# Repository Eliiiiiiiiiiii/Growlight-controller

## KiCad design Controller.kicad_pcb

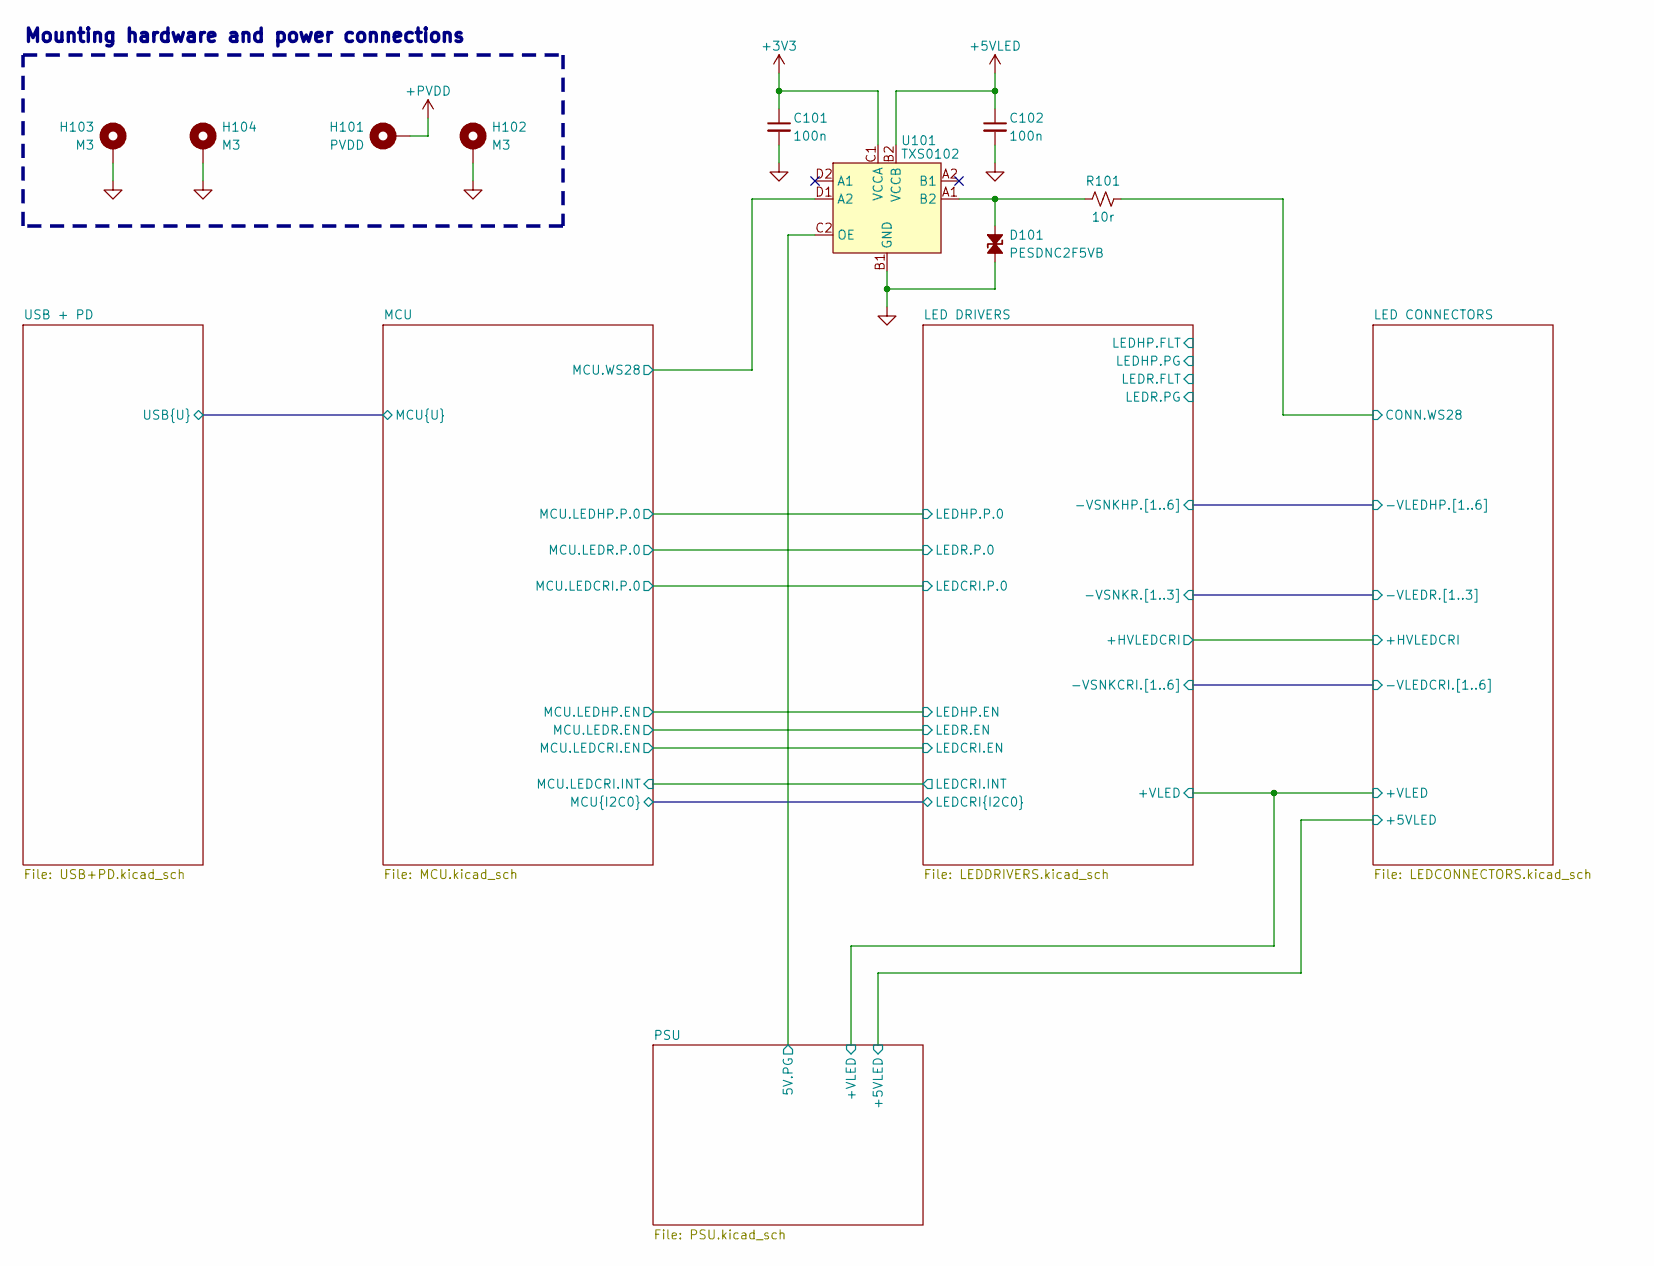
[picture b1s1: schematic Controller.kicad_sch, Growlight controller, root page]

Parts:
C101, C102: 100n; C 0402 (1005 Metric)
D101: PESDNC2F5VB; DFN-1006-2L
H101: PVDD; SMTSO3015CTJ
H102, H103, H104: M3; SMTSO3015CTJ
R101: 10r; R 0402 (1005 Metric)
U101: TXS0102; DSBGA-8 (0.9x1.9) P0.5

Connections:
+3V3: C101.1, U101.C1 (VCCA); also elsewhere on the board
+5VLED: C102.1, U101.B2 (VCCB); also elsewhere on the board
+PVDD: H101.1 (1_1); also elsewhere on the board
/LED CONNECTORS/CONN.WS28: R101.2; also elsewhere on the board
/MCU/MCU.WS28: U101.D1 (A2); also elsewhere on the board
/PSU/5V.PG: U101.C2 (OE); also elsewhere on the board
GND: C101.2, C102.2, D101.2 (A2), H102.1 (1_1), H103.1 (1_1), H104.1 (1_1), U101.B1 (GND); also elsewhere on the board
unnamed: D101.1 (A1), R101.1, U101.A1 (B2)

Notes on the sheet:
Mounting hardware and power connections

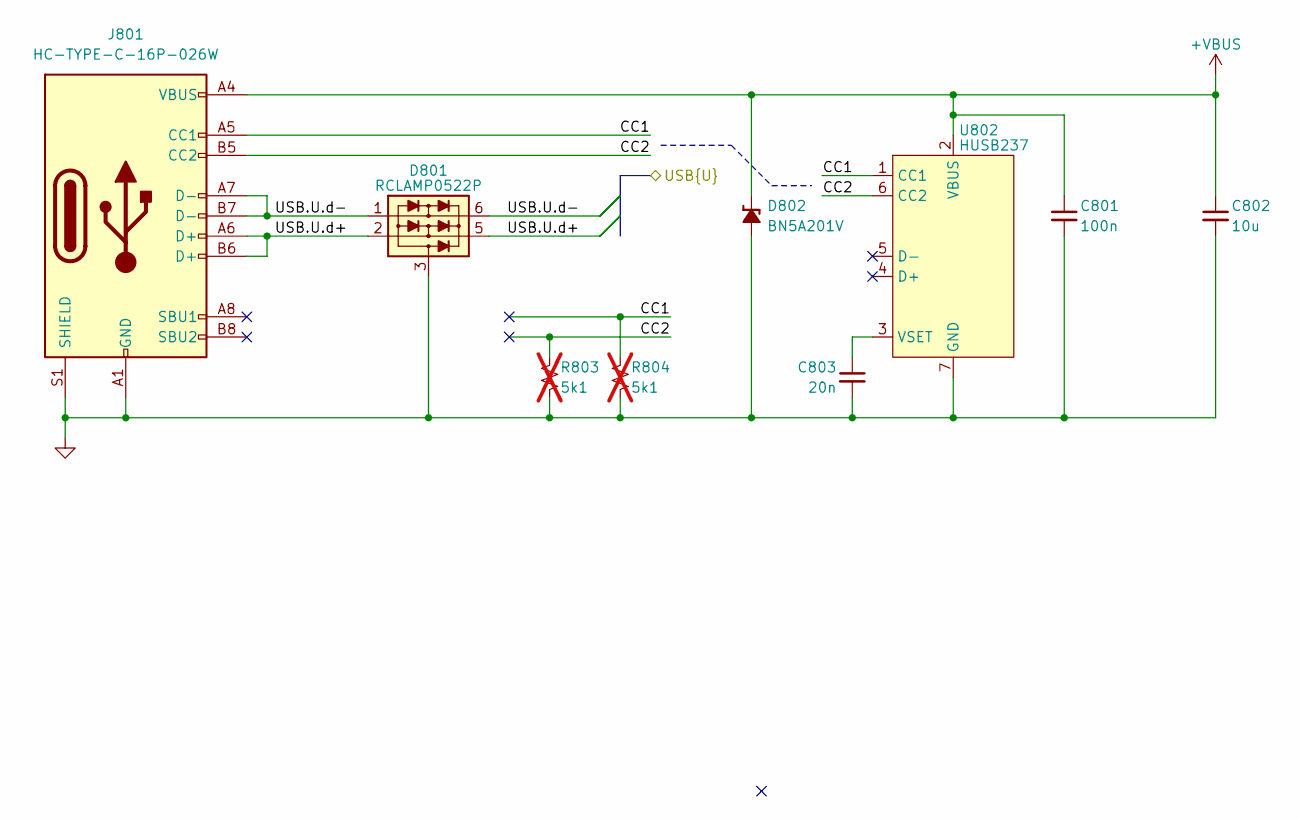
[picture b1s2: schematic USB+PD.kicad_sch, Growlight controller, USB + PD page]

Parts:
C801: 100n; C 0402 (1005 Metric)
C802: 10u; C 0805 (2012 Metric)
C803: 20n; C 0402 (1005 Metric)
D801: RCLAMP0522P; DFN1610-6L (1.6x1)
D802: BN5A201V; DFN1610-2L (1.6x1)
J801: HC-TYPE-C-16P-026W
R803, R804: 5k1; R 0402 (1005 Metric); not fitted
U802: HUSB237; SON-6 (2x2) P0.65

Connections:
+VBUS: C801.1, C802.1, D802.1 (K), J801.A4 (VBUS), J801.A9 (VBUS), J801.B4 (VBUS), J801.B9 (VBUS), U802.2 (VBUS); also elsewhere on the board
/MCU/MCU.U.d+: D801.2, D801.5, J801.A6 (D+), J801.B6 (D+); also elsewhere on the board
/MCU/MCU.U.d-: D801.1, D801.6, J801.A7 (D-), J801.B7 (D-); also elsewhere on the board
/USB + PD/CC1: J801.A5 (CC1), R804.1, U802.1 (CC1)
/USB + PD/CC2: J801.B5 (CC2), R803.1, U802.6 (CC2)
GND: C801.2, C802.2, C803.2, D801.3, D801.4, D802.2 (A), J801.A1 (GND), J801.A12 (GND), J801.B1 (GND), J801.B12 (GND), J801.S1 (SHIELD), R803.2, R804.2, U802.7 (GND); also elsewhere on the board
unnamed: C803.1, U802.3 (VSET)

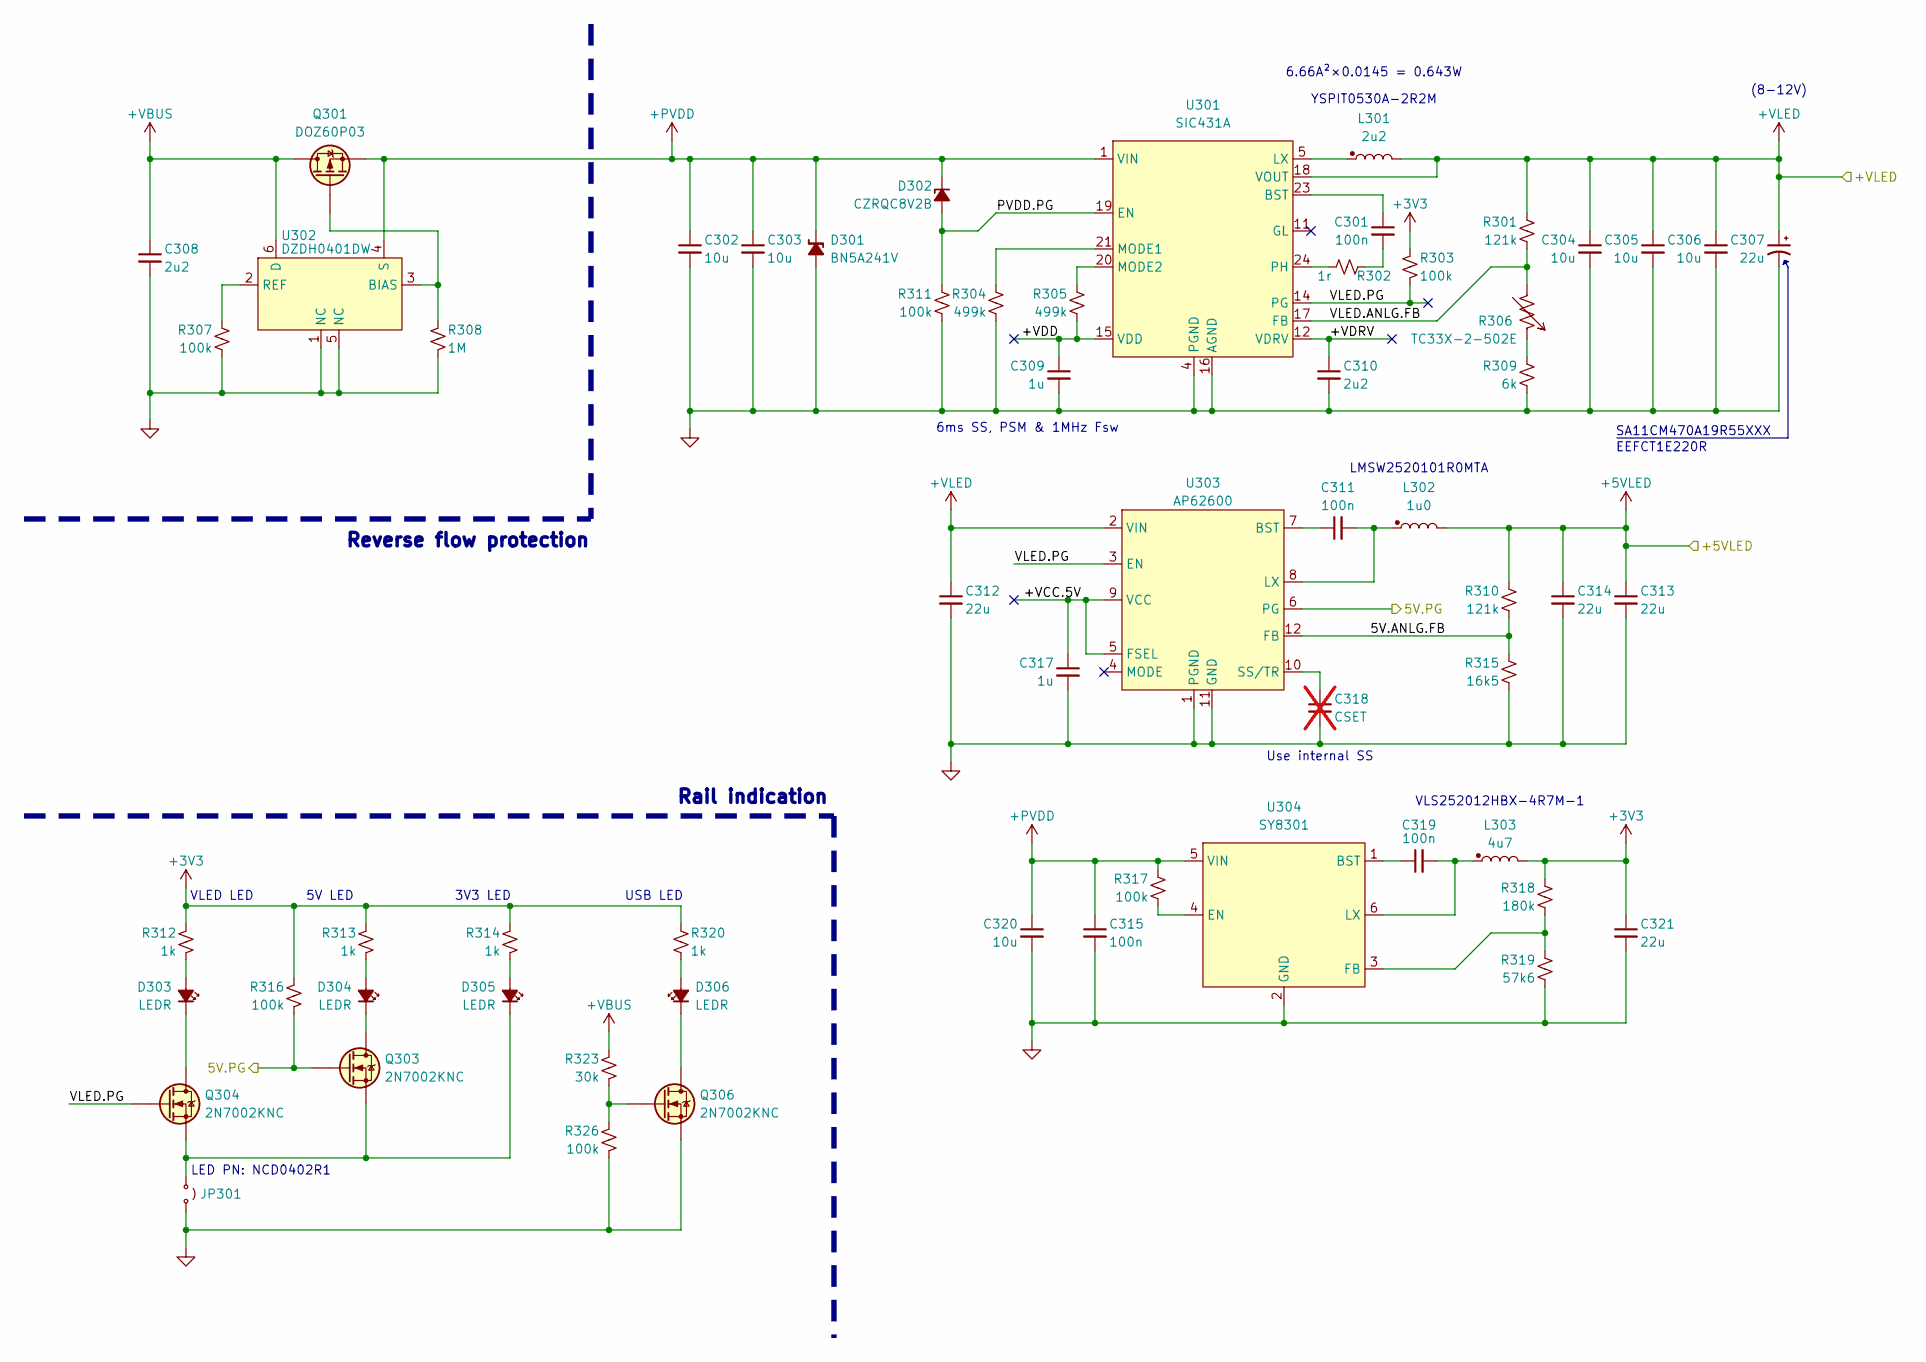
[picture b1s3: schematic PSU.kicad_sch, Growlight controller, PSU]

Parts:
C301, C311, C315, C319: 100n; C 0402 (1005 Metric)
C302, C303, C304, C305, C306, C320: 10u; C 0805 (2012 Metric)
C307: 22u; CP Flat (7.3x4.3) H1.4 muRata
C308, C310: 2u2; C 0603 (1608 Metric)
C309, C317: 1u; C 0402 (1005 Metric)
C312, C313, C314, C321: 22u; C 0805 (2012 Metric)
C318: CSET; C 0402 (1005 Metric); not fitted
D301: BN5A241V; DFN1610-2L (1.6x1)
D302: CZRQC8V2B; DFN-1006-2L
D303, D304, D305, D306: LEDR; LED-0402-R
JP301: Jumper_2_Small_Open; Jumper-NO 2P (1.9x1.4)
L301: 2u2; YSPIT0530A
L302: 1u0; LMSW252010
L303: 4u7; VLS252012
Q301: DOZ60P03; DFN-8 (3x3) 1EP
Q303, Q304, Q306: 2N7002KNC; DFN-1006-3L
R301, R310: 121k; R 0402 (1005 Metric)
R302: 1r; R 0402 (1005 Metric)
R303, R307, R311, R316, R317, R326: 100k; R 0402 (1005 Metric)
R304, R305: 499k; R 0402 (1005 Metric)
R306: TC33X-2-502E; TC33X-x-xxxx
R308: 1M; R 0402 (1005 Metric)
R309: 6k; R 0402 (1005 Metric)
R312, R313, R314, R320: 1k; R 0402 (1005 Metric)
R315: 16k5; R 0402 (1005 Metric)
R318: 180k; R 0402 (1005 Metric)
R319: 57k6; R 0402 (1005 Metric)
R323: 30k; R 0402 (1005 Metric)
U301: SIC431A; MLP44-24L (4x4) P0.45 Vishay
U302: DZDH0401DW; SOT-363
U303: AP62600; VQFN2030-12 (2x3) P0.5 DIODES
U304: SY8301; SOT-23-6

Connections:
+3V3: C321.1, L303.2, R303.1, R312.2, R313.2, R314.2, R316.2, R318.1, R320.2; also elsewhere on the board
+5VLED: C313.1, C314.1, L302.2, R310.1; also elsewhere on the board
+PVDD: C302.1, C303.1, C315.1, C320.1, D301.1 (K), D302.1 (K), Q301.1 (S), Q301.2 (S), Q301.3 (S), R317.1, U301.1 (VIN), U301.2 (VIN), U301.22 (VIN), U301.26 (VIN), U302.4 (S), U304.5 (VIN); also elsewhere on the board
+VBUS: C308.1, Q301.5 (D), R323.2, U302.6 (D); also elsewhere on the board
+VLED: C304.1, C305.1, C306.1, C307.1, C312.1, L301.2, R301.1, U301.18 (VOUT), U303.2 (VIN); also elsewhere on the board
/PSU/5V.ANLG.FB: R310.2, R315.1, U303.12 (FB)
/PSU/5V.PG: Q303.1 (G), R316.1, U303.6 (PG); also elsewhere on the board
/PSU/+VCC.5V: C317.1, U303.5 (FSEL), U303.9 (VCC)
/PSU/+VDD: C309.1, R305.2, U301.15 (VDD)
/PSU/+VDRV: C310.1, U301.12 (VDRV)
/PSU/PVDD.PG: D302.2 (A), R311.1, U301.19 (EN)
/PSU/VLED.ANLG.FB: R301.2, R306.2, U301.17 (FB)
/PSU/VLED.PG: Q304.1 (G), R303.2, U301.14 (PG), U303.3 (EN)
GND: C302.2, C303.2, C304.2, C305.2, C306.2, C307.2, C308.2, C309.2, C310.2, C312.2, C313.2, C314.2, C315.2, C317.2, C318.2, C320.2, C321.2, D301.2 (A), JP301.1 (A), Q306.2 (S), R304.2, R307.2, R308.2, R309.2, R311.2, R315.2, R319.2, R326.1, U301.3 (PGND), U301.4 (PGND), U301.13 (PGND), U301.16 (AGND), U301.25 (AGND), U301.27 (PGND), U302.1 (NC), U302.5 (NC), U303.1 (PGND), U303.11 (GND), U304.2 (GND); also elsewhere on the board
unnamed: C301.2, R302.2
unnamed: D303.2 (A), R312.1
unnamed: D303.1 (K), Q304.3 (D)
unnamed: D304.2 (A), R313.1
unnamed: D304.1 (K), Q303.3 (D)
unnamed: D305.2 (A), R314.1
unnamed: D305.1 (K), JP301.2 (B), Q303.2 (S), Q304.2 (S)
unnamed: D306.2 (A), R320.1
unnamed: D306.1 (K), Q306.3 (D)
unnamed: L301.1, U301.5 (LX), U301.6 (LX), U301.7 (LX), U301.8 (LX), U301.9 (LX)
unnamed: Q301.4 (G), R308.1, U302.3 (BIAS)
unnamed: Q306.1 (G), R323.1, R326.2
unnamed: R306.1, R309.1
unnamed: C301.1, U301.23 (BST)
unnamed: R304.1, U301.21 (MODE1)
unnamed: R305.1, U301.20 (MODE2)
unnamed: R302.1, U301.24 (PH)
unnamed: R307.1, U302.2 (REF)
unnamed: C311.1, U303.7 (BST)
unnamed: C311.2, L302.1, U303.8 (LX)
unnamed: C318.1, U303.10 (SS/TR)
unnamed: C319.1, U304.1 (BST)
unnamed: R317.2, U304.4 (EN)
unnamed: R318.2, R319.1, U304.3 (FB)
unnamed: C319.2, L303.1, U304.6 (LX)

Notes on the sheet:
5V LED
Reverse flow protection
VLS252012HBX-4R7M-1
LED PN: NCD0402R1
USB LED
3V3 LED
EEFCT1E220R
(8-12V)
Rail indication
YSPIT0530A-2R2M
SA11CM470A19R55XXX
VLED LED
LMSW2520101R0MTA
6.66A²×0.0145 = 0.643W
6ms SS, PSM & 1MHz Fsw
Use internal SS

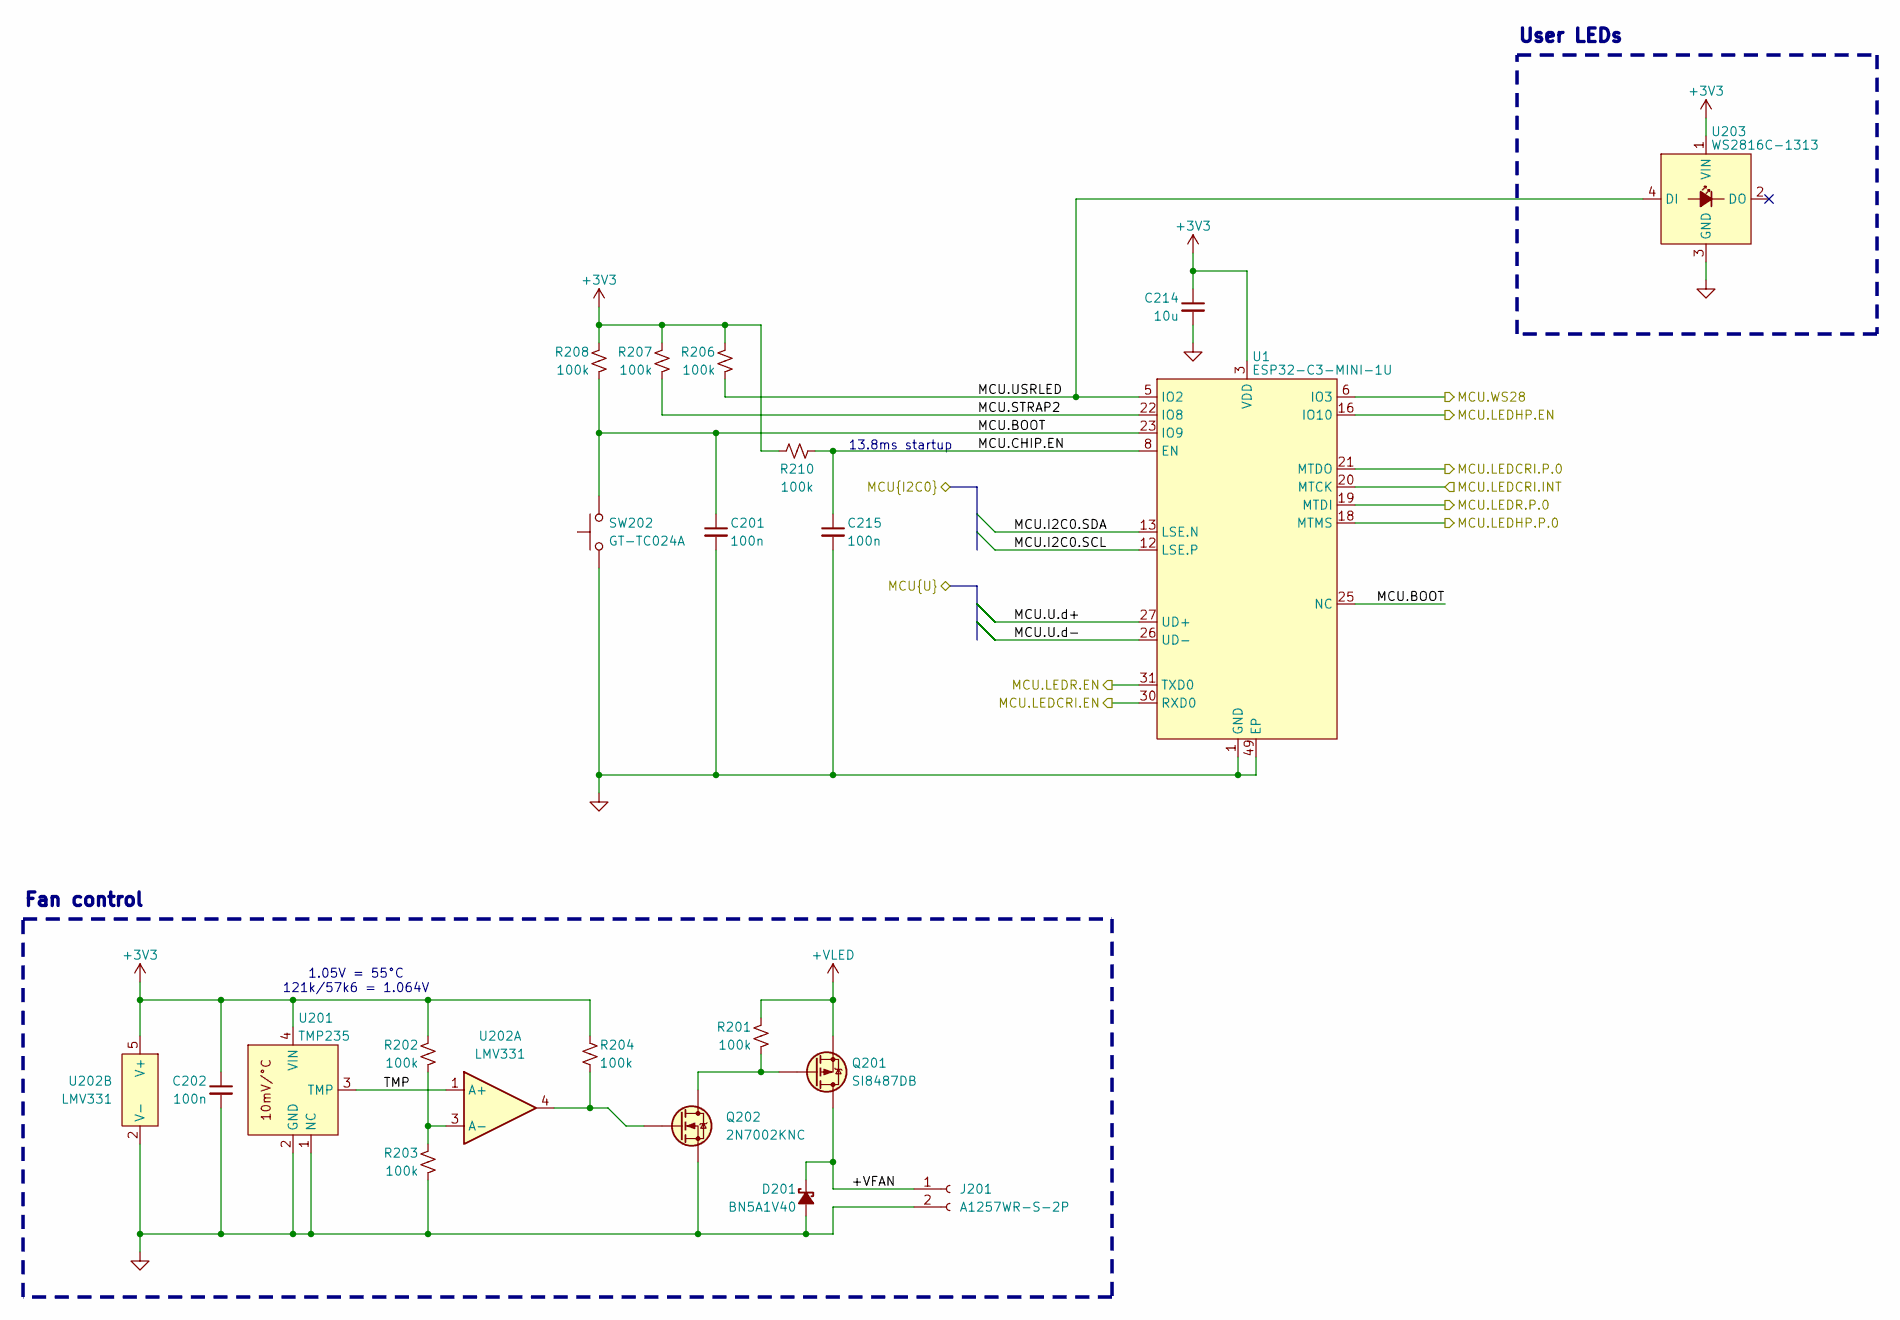
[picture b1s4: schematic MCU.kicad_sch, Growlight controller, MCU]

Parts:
C201, C202, C215: 100n; C 0402 (1005 Metric)
C214: 10u; C 0805 (2012 Metric)
D201: BN5A1V40; DFN1610-2L (1.6x1)
J201: A1257WR-S-2P; A1257WR-S-2P (GH)
Q201: SI8487DB; WLCSP-4 (1.56x1.56) P0.8
Q202: 2N7002KNC; DFN-1006-3L
R201, R202, R203, R204, R206, R207, R208, R210: 100k; R 0402 (1005 Metric)
SW202: GT-TC024A; GT-TC024A-H0060-L1
U1: ESP32-C3-MINI-1U
U201: TMP235; SOT-363-5
U202: LMV331; SOT-363-5
U203: WS2816C-1313; WS2816C-1313 4P

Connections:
+3V3: C202.1, C214.1, R202.2, R204.2, R206.2, R207.2, R208.2, R210.1, U1.3 (VDD), U201.4 (VIN), U202.5 (V+), U203.1 (VIN); also elsewhere on the board
+VLED: Q201.4 (S), R201.2; also elsewhere on the board
/LED DRIVERS/LEDCRI.EN: U1.30 (RXD0); also elsewhere on the board
/LED DRIVERS/LEDCRI.I2C0.SCL: U1.12 (LSE.P); also elsewhere on the board
/LED DRIVERS/LEDCRI.I2C0.SDA: U1.13 (LSE.N); also elsewhere on the board
/LED DRIVERS/LEDCRI.INT: U1.20 (MTCK); also elsewhere on the board
/LED DRIVERS/LEDCRI.P.0: U1.21 (MTDO); also elsewhere on the board
/LED DRIVERS/LEDHP.EN: U1.16 (IO10); also elsewhere on the board
/LED DRIVERS/LEDHP.P.0: U1.18 (MTMS); also elsewhere on the board
/LED DRIVERS/LEDR.EN: U1.31 (TXD0); also elsewhere on the board
/LED DRIVERS/LEDR.P.0: U1.19 (MTDI); also elsewhere on the board
/MCU/+VFAN: D201.1 (K), J201.1, Q201.2 (D), Q201.3 (D)
/MCU/MCU.BOOT: C201.1, R208.1, SW202.2, U1.23 (IO9), U1.25 (NC)
/MCU/MCU.CHIP.EN: C215.1, R210.2, U1.8 (EN)
/MCU/MCU.STRAP2: R207.1, U1.22 (IO8)
/MCU/MCU.U.d+: U1.27 (UD+); also elsewhere on the board
/MCU/MCU.U.d-: U1.26 (UD-); also elsewhere on the board
/MCU/MCU.USRLED: R206.1, U1.5 (IO2), U203.4 (DI)
/MCU/MCU.WS28: U1.6 (IO3); also elsewhere on the board
/MCU/TMP: U201.3 (TMP), U202.1 (A+)
GND: C201.2, C202.2, C214.2, C215.2, D201.2 (A), J201.2, Q202.2 (S), R203.1, SW202.1, U1.1 (GND), U1.2 (GND), U1.11 (GND), U1.14 (GND), U1.36 (GND), U1.37 (GND), U1.38 (GND), U1.39 (GND), U1.40 (GND), U1.41 (GND), U1.42 (GND), U1.43 (GND), U1.44 (GND), U1.45 (GND), U1.46 (GND), U1.47 (GND), U1.48 (GND), U1.49 (EP), U1.50 (GND), U1.51 (GND), U1.52 (GND), U1.53 (GND), U201.1 (NC), U201.2 (GND), U201.5 (NC), U202.2 (V-), U203.3 (GND); also elsewhere on the board
unnamed: Q201.1 (G), Q202.3 (D), R201.1
unnamed: Q202.1 (G), R204.1, U202.4
unnamed: R202.1, R203.2, U202.3 (A-)

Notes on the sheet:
1.05V = 55°C 121k/57k6 = 1.064V
User LEDs
13.8ms startup
Fan control

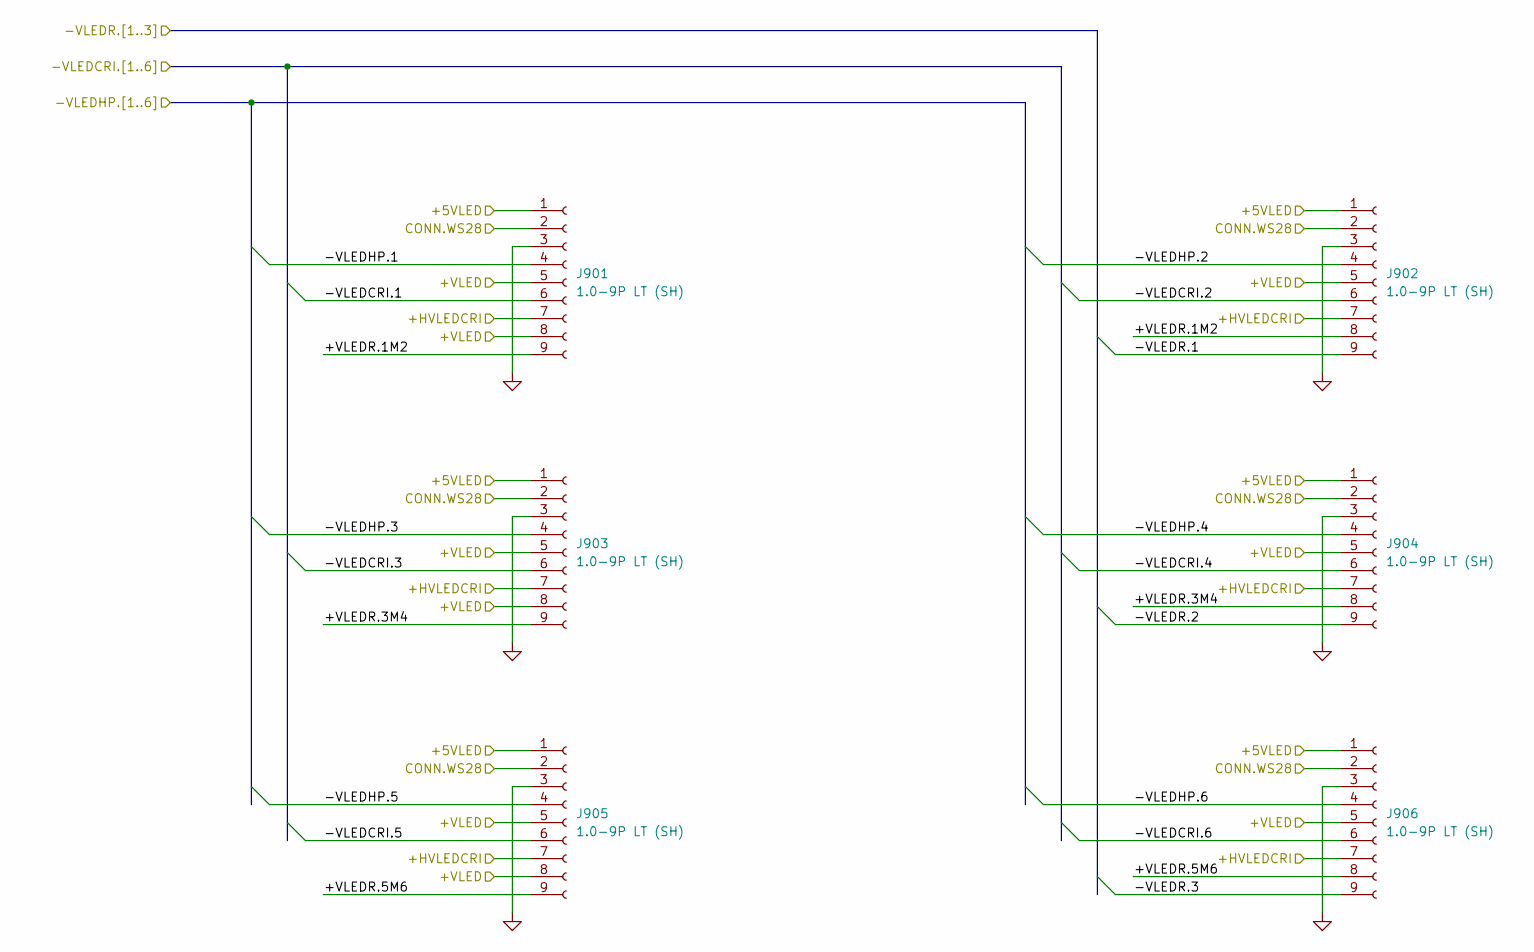
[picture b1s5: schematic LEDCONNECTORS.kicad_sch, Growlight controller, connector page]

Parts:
J901, J902, J903, J904, J905, J906: 1.0-9P LT (SH)

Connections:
+5VLED: J901.1, J902.1, J903.1, J904.1, J905.1, J906.1; also elsewhere on the board
+HVLEDCRI: J901.7, J902.7, J903.7, J904.7, J905.7, J906.7; also elsewhere on the board
+VLED: J901.5, J901.8, J902.5, J903.5, J903.8, J904.5, J905.5, J905.8, J906.5; also elsewhere on the board
/LED CONNECTORS/+VLEDR.1M2: J901.9, J902.8
/LED CONNECTORS/+VLEDR.3M4: J903.9, J904.8
/LED CONNECTORS/+VLEDR.5M6: J905.9, J906.8
/LED CONNECTORS/-VLEDCRI.1: J901.6; also elsewhere on the board
/LED CONNECTORS/-VLEDCRI.2: J902.6; also elsewhere on the board
/LED CONNECTORS/-VLEDCRI.3: J903.6; also elsewhere on the board
/LED CONNECTORS/-VLEDCRI.4: J904.6; also elsewhere on the board
/LED CONNECTORS/-VLEDCRI.5: J905.6; also elsewhere on the board
/LED CONNECTORS/-VLEDCRI.6: J906.6; also elsewhere on the board
/LED CONNECTORS/-VLEDHP.1: J901.4; also elsewhere on the board
/LED CONNECTORS/-VLEDHP.2: J902.4; also elsewhere on the board
/LED CONNECTORS/-VLEDHP.3: J903.4; also elsewhere on the board
/LED CONNECTORS/-VLEDHP.4: J904.4; also elsewhere on the board
/LED CONNECTORS/-VLEDHP.5: J905.4; also elsewhere on the board
/LED CONNECTORS/-VLEDHP.6: J906.4; also elsewhere on the board
/LED CONNECTORS/-VLEDR.1: J902.9; also elsewhere on the board
/LED CONNECTORS/-VLEDR.2: J904.9; also elsewhere on the board
/LED CONNECTORS/-VLEDR.3: J906.9; also elsewhere on the board
/LED CONNECTORS/CONN.WS28: J901.2, J902.2, J903.2, J904.2, J905.2, J906.2; also elsewhere on the board
GND: J901.3, J902.3, J903.3, J904.3, J905.3, J906.3; also elsewhere on the board

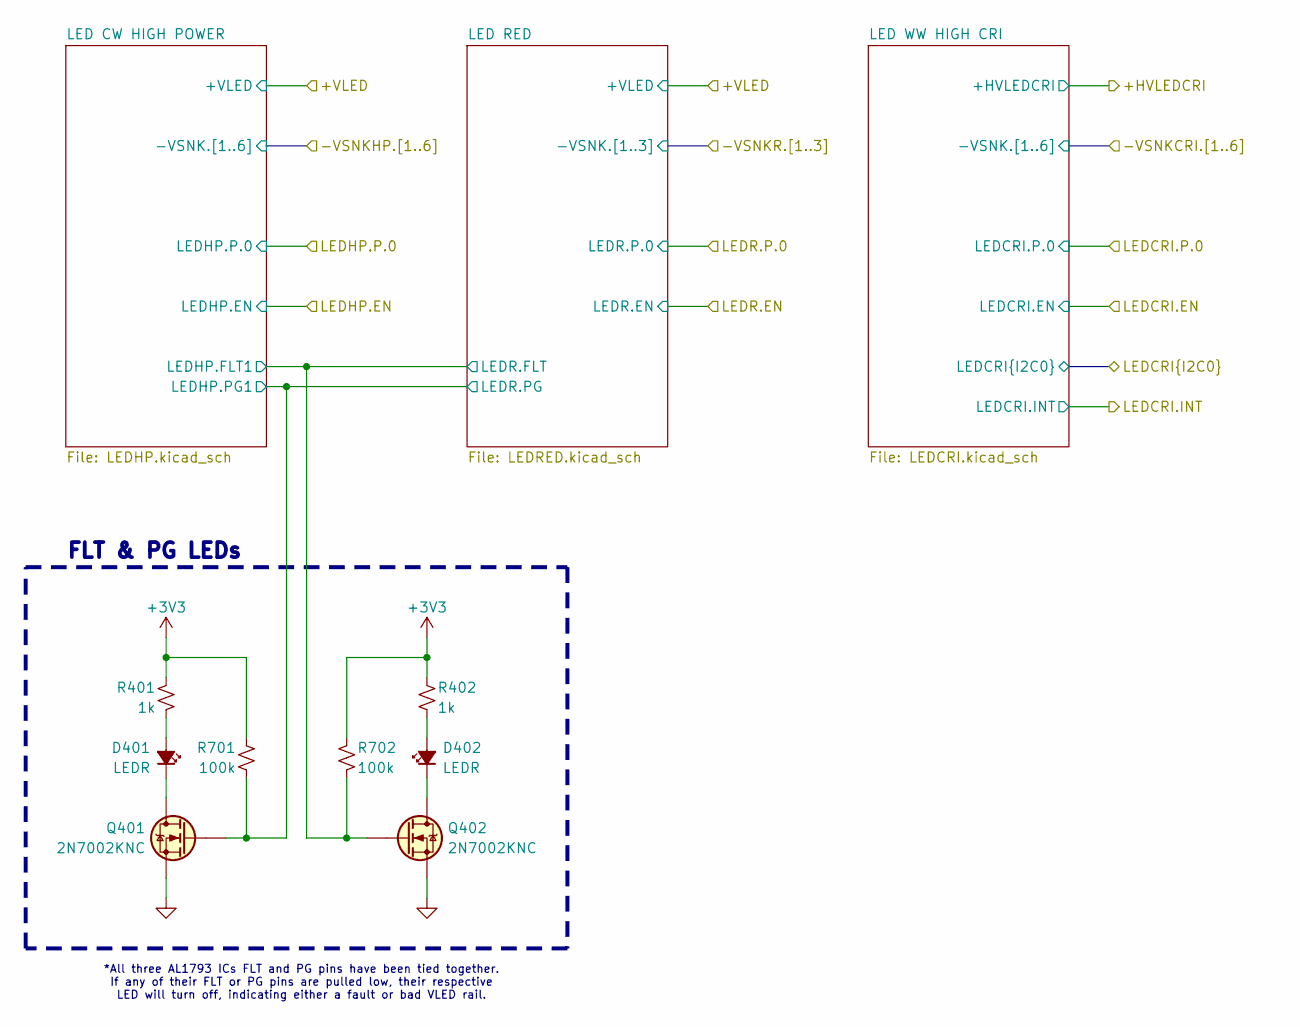
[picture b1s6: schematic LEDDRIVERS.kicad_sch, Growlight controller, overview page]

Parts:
D401, D402: LEDR; LED-0402-R
Q401, Q402: 2N7002KNC; DFN-1006-3L
R401, R402: 1k; R 0402 (1005 Metric)
R701, R702: 100k; R 0402 (1005 Metric)

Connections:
+3V3: R401.2, R402.2, R701.1, R702.1; also elsewhere on the board
/LED DRIVERS/LED CW HIGH POWER/LEDHP.FLT1: Q402.1 (G), R702.2; also elsewhere on the board
/LED DRIVERS/LED CW HIGH POWER/LEDHP.PG1: Q401.1 (G), R701.2; also elsewhere on the board
GND: Q401.2 (S), Q402.2 (S); also elsewhere on the board
unnamed: D401.2 (A), R401.1
unnamed: D401.1 (K), Q401.3 (D)
unnamed: D402.2 (A), R402.1
unnamed: D402.1 (K), Q402.3 (D)

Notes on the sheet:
*All three AL1793 ICs FLT and PG pins have been tied together. If any of their FLT or PG pins are pulled low, their respective LED will turn off, indicating either a fault or bad VLED rail.
FLT & PG LEDs

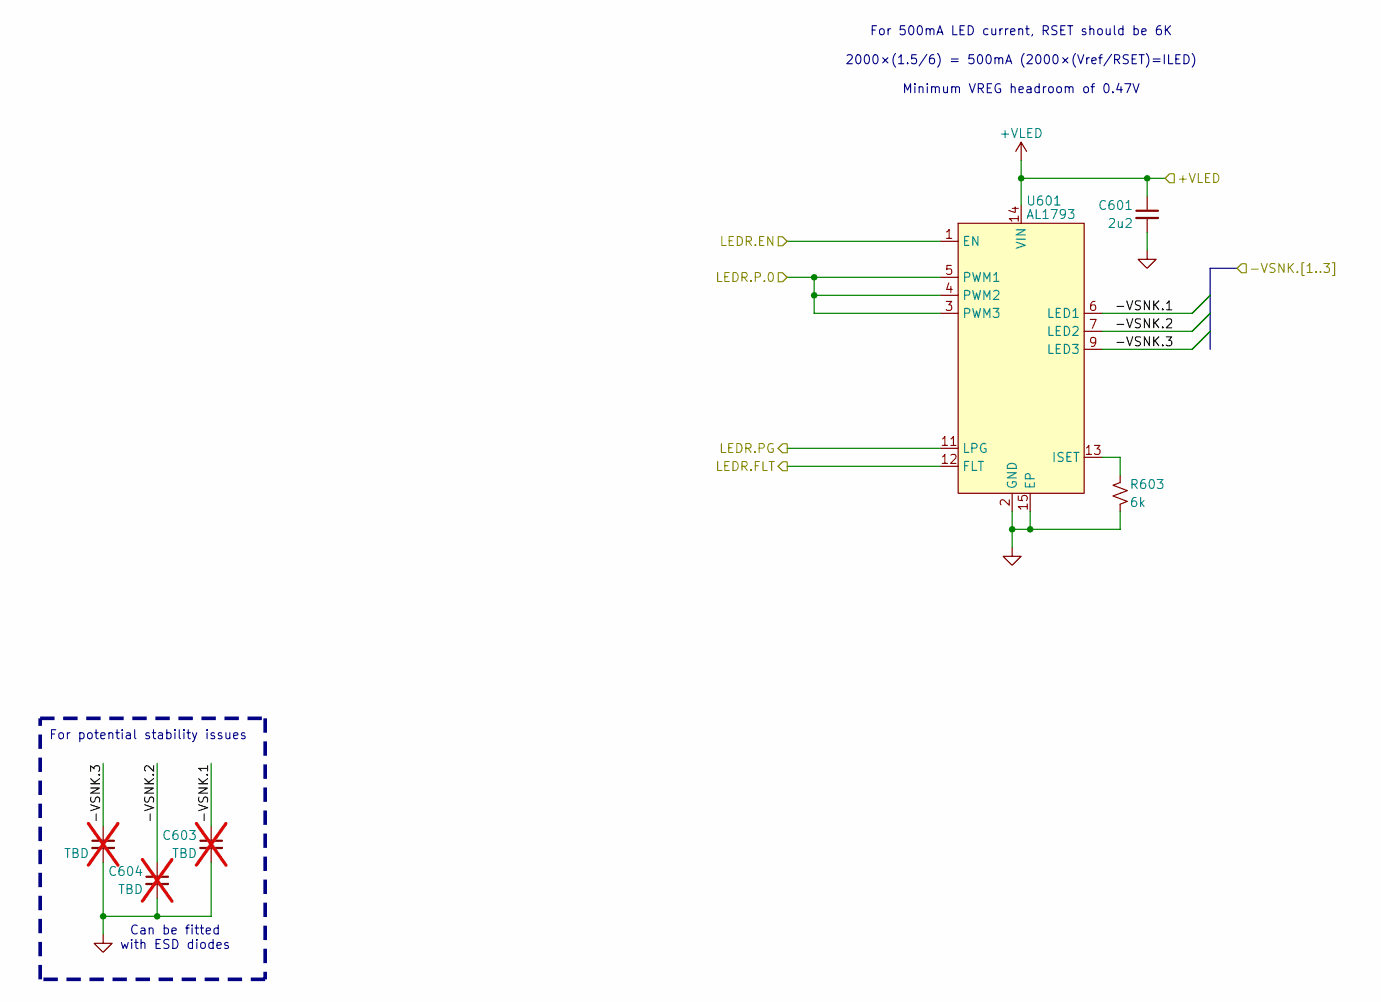
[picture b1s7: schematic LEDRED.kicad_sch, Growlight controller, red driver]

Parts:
C601: 2u2; C 0603 (1608 Metric)
C602, C603, C604: TBD; C 0402 (1005 Metric); not fitted
R603: 6k; R 0402 (1005 Metric)
U601: AL1793; UDFN4030-14 (3x4) 1EP

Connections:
+VLED: C601.1, U601.14 (VIN); also elsewhere on the board
/LED CONNECTORS/-VLEDR.1: C603.1, U601.6 (LED1); also elsewhere on the board
/LED CONNECTORS/-VLEDR.2: C604.1, U601.7 (LED2); also elsewhere on the board
/LED CONNECTORS/-VLEDR.3: C602.1, U601.9 (LED3); also elsewhere on the board
/LED DRIVERS/LED CW HIGH POWER/LEDHP.FLT1: U601.12 (FLT); also elsewhere on the board
/LED DRIVERS/LED CW HIGH POWER/LEDHP.PG1: U601.11 (LPG); also elsewhere on the board
/LED DRIVERS/LEDR.EN: U601.1 (EN); also elsewhere on the board
/LED DRIVERS/LEDR.P.0: U601.3 (PWM3), U601.4 (PWM2), U601.5 (PWM1); also elsewhere on the board
GND: C601.2, C602.2, C603.2, C604.2, R603.2, U601.2 (GND), U601.8 (GND), U601.10 (GND), U601.15 (EP); also elsewhere on the board
unnamed: R603.1, U601.13 (ISET)

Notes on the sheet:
For potential stability issues
Can be fitted with ESD diodes
For 500mA LED current, RSET should be 6K 2000×(1.5/6) = 500mA (2000×(Vref/RSET)=ILED) Minimum VREG headroom of 0.47V

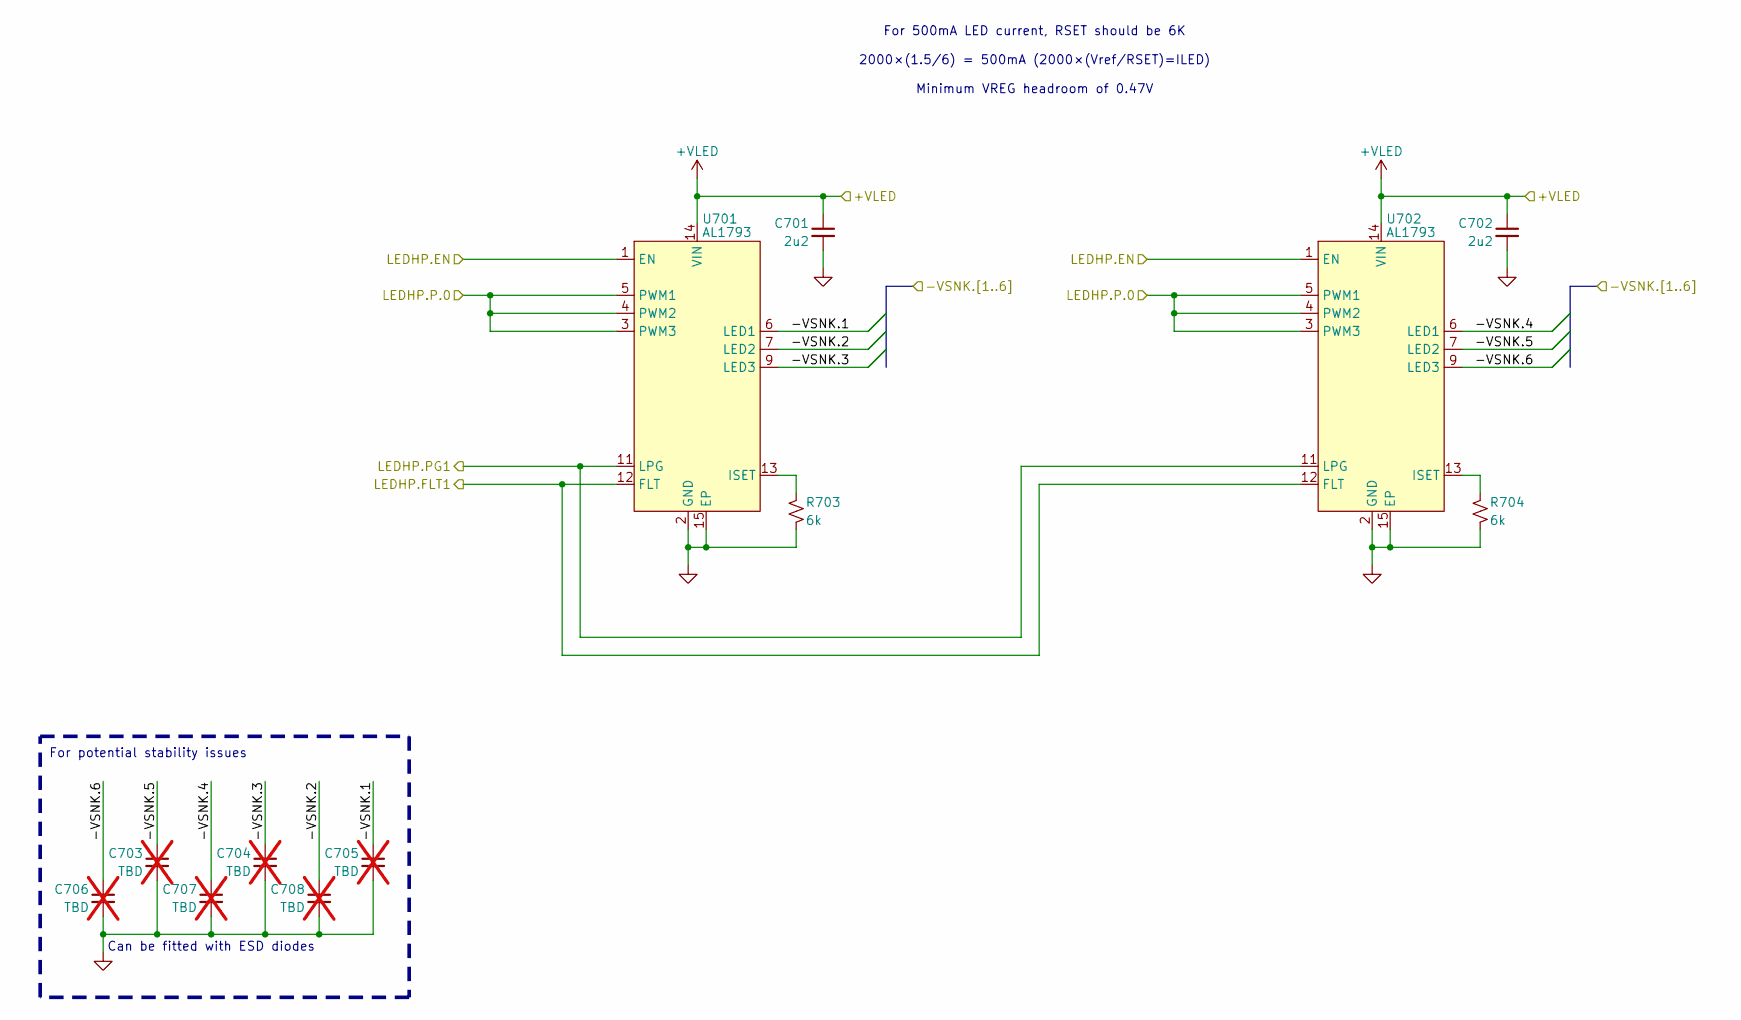
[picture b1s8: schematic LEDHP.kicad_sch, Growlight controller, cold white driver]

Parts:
C701, C702: 2u2; C 0603 (1608 Metric)
C703, C704, C705, C706, C707, C708: TBD; C 0402 (1005 Metric); not fitted
R703, R704: 6k; R 0402 (1005 Metric)
U701, U702: AL1793; UDFN4030-14 (3x4) 1EP

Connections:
+VLED: C701.1, C702.1, U701.14 (VIN), U702.14 (VIN); also elsewhere on the board
/LED CONNECTORS/-VLEDHP.1: C705.1, U701.6 (LED1); also elsewhere on the board
/LED CONNECTORS/-VLEDHP.2: C708.1, U701.7 (LED2); also elsewhere on the board
/LED CONNECTORS/-VLEDHP.3: C704.1, U701.9 (LED3); also elsewhere on the board
/LED CONNECTORS/-VLEDHP.4: C707.1, U702.6 (LED1); also elsewhere on the board
/LED CONNECTORS/-VLEDHP.5: C703.1, U702.7 (LED2); also elsewhere on the board
/LED CONNECTORS/-VLEDHP.6: C706.1, U702.9 (LED3); also elsewhere on the board
/LED DRIVERS/LED CW HIGH POWER/LEDHP.FLT1: U701.12 (FLT), U702.12 (FLT); also elsewhere on the board
/LED DRIVERS/LED CW HIGH POWER/LEDHP.PG1: U701.11 (LPG), U702.11 (LPG); also elsewhere on the board
/LED DRIVERS/LEDHP.EN: U701.1 (EN), U702.1 (EN); also elsewhere on the board
/LED DRIVERS/LEDHP.P.0: U701.3 (PWM3), U701.4 (PWM2), U701.5 (PWM1), U702.3 (PWM3), U702.4 (PWM2), U702.5 (PWM1); also elsewhere on the board
GND: C701.2, C702.2, C703.2, C704.2, C705.2, C706.2, C707.2, C708.2, R703.2, R704.2, U701.2 (GND), U701.8 (GND), U701.10 (GND), U701.15 (EP), U702.2 (GND), U702.8 (GND), U702.10 (GND), U702.15 (EP); also elsewhere on the board
unnamed: R703.1, U701.13 (ISET)
unnamed: R704.1, U702.13 (ISET)

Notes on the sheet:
Can be fitted with ESD diodes
For 500mA LED current, RSET should be 6K 2000×(1.5/6) = 500mA (2000×(Vref/RSET)=ILED) Minimum VREG headroom of 0.47V
For potential stability issues
